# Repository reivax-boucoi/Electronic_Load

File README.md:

# Electronic Load

This repository hosts my work in developping a custom electronic load from scratch. 
For more information on what an electronic load does and what it can be used for, see [this](https://www.mouser.com/pdfdocs/DC_Electronic_Load_Application_Note.pdf). 

Specifically, this load targets DC-DC converters testing, as it includes input and output power monitoring.

I you have any question on this repository, feel free to contact the owner at (reivax[dot]boucoi[at]laposte[dot]net).

Featured on [Hackaday](https://hackaday.com/2020/06/06/a-diy-electronic-load-with-a-twist/) and [Electronics-Lab](https://www.electronics-lab.com/diy-electronic-load-dc-dc-converter-characterization/)!

---
---

### Features

* Constant Current, Power and Resistance modes
* Battery capacity logging with adjustable cutoff voltage
* Input and output power logging : instant efficiency reading for DC-DC converters
* Rotary encoder driven interface
* Dedicated Load ON/OFF button
* Intuitive LCD menu system with editable values
* 12bit current, voltage and power measurements 
* 30W continuous sinking capability, 250W peak
* Temperature controlled fan with auto shutdown.
* Adjustable acquistion rate
* 115200 bauds serial communication through USB with a PC (non-isolated !)

### Specifications
> Enough talk, give us the specs, son !

Altough the device has not been fully qualified through systematic testing, here are the basic specs you can expect. 
* Input voltage range : 0 - 100V DC maximum, 2-80V DC regulating
* Supply voltage range : 0 - 16V maximum, 12V nominal 
* Device current consumption : 50mA nominal (0.6W)
* Load current range : 5mA - 5.25A, in 8mA steps
* Current regulation : 5% +/- 8mA typical @ 8kHz bandwidth
* Transient response : rise time < 20µs/A, overshoot < 2%
* Constant Power/Resistance regulation bandwidth : 10Hz

---
---

## Schematic and Layout
The heart of the system is an Atmel ATmega328P AVR microcontroller with 32kB of Flash and 2k of RAM running at a whopping 16MHz. It interfaces an I2C 12bit DAC (the MCP47FEB21A1) and the LTC2992 dual power monitor chip.

The USB serial interface uses the MCP2221A bridge. The display is a classic 16x2 LCD.

On the analog part, 10mΩ  and 0.2Ω shunt resistors are used, coupled with two W9NK90Z N-ch power MOSFETS. The heatsink was salvaged from an old graphics card. Attached are a 10k NTC and a generic fan (12v @ 200mA, 80mm). Current regulation is achieved through the help of a MCP6H02 opamp, and a carefully designed feedback network which guarantees the specified rise time with little to no overshoot.

The layout was done using the Eagle software (v9.5.2). Gerbers, Eagle project files, top and bottom views are available on the `pcb` folder. PCBs were printed using JLCPCB service.
The schematic is available in a pdf and Eagle `.sch` format as well. A Bill of Materials (BOM) is also available, in plain text and html format, on the `pcb` folder.

Several user-definable bi-color status LEDs are included, such as Load ON/OFF, TX & RX, acquisition blink, as well as a power LED.

An expansion/debug port is provided, with +5V, ground, I2C and UART available.

There are several issues regarding the layout of the PCB, as it is a first version. Improper Kelvin connections to the current sense resistors, or wrong hole size for the power input connector by example. The heatsink originally used is salvaged from old equipement and the footprint may not be relevant to anyone else. Space for rubber feet placement should be included. Also, the LCD is too close to the heatsink, which is impractical during assembly (especially accessing the fan and temp sensor connector).

---
---

## Firmware
The firmware for this device is currently in revision 1.3. It is written for a barebone ATmega328p Atmel microcontroller.

```18604 bytes (60%) of program storage space. Maximum is 30720 bytes.```

```1635 bytes (79%) of dynamic memory, 413 bytes left. Maximum is 2048 bytes.```

As you can see it's not the lightest firmware, mostly due to the use of the `Wire` and `LCD` librairies from Arduino, which are bulky. However, there is still enough room for future improvements. Just keep in mind if you want to improve the project to leave space for local variables allocation.

---

### Programming
An ISP port is provided on the board, making reflashing easy. All you need is an AVR-compatible programmer with the standard 10 pins ICSP header. I used the very good (and very cheap!) [Usbasp](https://www.fischl.de/usbasp/) during developpement. Avrdude can be used to download the pre-compiled binary `main.hex`, or you can compile the project yourself first.
`Avr Fuses settings :(E:FD, H:DE, L:FF)`

To program the chip, execute : `avrdude -p m328p -c usbasp -P usb -U flash:w:firmware/main.hex`

---

### Software structure

* Display related stuff : `Screen.cpp`, `Menu.cpp`
* LTC2992 power monitoring stuff : `PM.cpp`
* DC Load stuff : `Load.cpp`
* Generic io interfacing : `Utils.cpp`, `SimpleRotary.cpp`, `Wire.cpp`, `LCD.cpp`
* Control loop and display update : `main.cpp`

---

### Usage
First apply power to the device through USB (for limited load capacity) or, better, 12V DC on the input power jack (beware of polarity).

The welcome screen pops up with the following menus : 

* Load allows you to set the load parameters and mode (CC/CP/CR)
* Battery enters the battery capacity mode
* Meter measures input power
* Settings is self explanatory

Turn the rotary encoder to cycle through the menus and screens, and push to enter. At any time use the back button (to the right of the encoder) to get back to the previous menu or exit editing mode. 

Editing a value starts by selecting the value to edit. Press enter on a screen, you should get a flashing square in front of a value. Turn the knob until the desired value is selected. Press enter to edit. The leftmost digit is selected. To change the edited digit, press enter once again. Press back to validate. 

**You will have to restart the load in order for the changes to take effect.** This is done to prevent happy little accidents. To start and stop the load, press the rightmost button. The blue LED should light up. Is the LED turns red, a fault occured. Faults can happen if :
* The heatsink temperature exceeds the hard temperature stop defined in `Load.h`
* The load fails to regulate. This will mostly be caused by the DUT hiccuping (or sharp V/I curve), or insufficent power to the Electronic Load.

The load menu has 4 screens : 

The last screen shows the power lost in the DUT (Pr), the efficency, the input and output voltages of the converter.

The load mode (CC/CP/CR) is determined by the screen displayed when the load is started. If the screen is not one of the CC/CP/CR screens, is starts in the previously used mode.

Here is what the Battery screen looks like :

Set the discharge current I and the cutoff voltage Vc before starting the load with the rightmost button. Accumulated capacity in Wh and Ah are displayed. The load will automatically shut off when the input voltage is below the cutoff voltage. The total capacity will remain displayed until the load is restarted in this mode.

The meter screen shows the input measurements :

The settings screen alows to modify various parameters : 

It monitors the supply voltage and you can change the threshold temperature for the fan, as well as the refresh rate of the screen. Note that the load has a hard temperature stop defined in `Load.h`, and a maximum refresh rate of approx 10Hz.

---
---

## Improvements

- [x] Design a mechanical mount for the fan / stabilize the board
- [x] Re-think the menu system to be more modular / lower size
- WIP Add logging capability with serial interface
- WIP Add current sweep programming for DC-DC converters automatic characterization (with di/dv auto resolution)
* Fix the minimum current issue (currently min is 5mA)
* Fix the 4 terminal Kelvin connection on the 10mΩ current sense resistors in the PCB layout
* Design a usb isolator companion board or add SD card logging addon on i2c bus.
* Design 4.5V->12V boost addon to allow full operation from usb power
* Better code commenting
* Save last used confguration on EEPROM for next power-up.
* ...

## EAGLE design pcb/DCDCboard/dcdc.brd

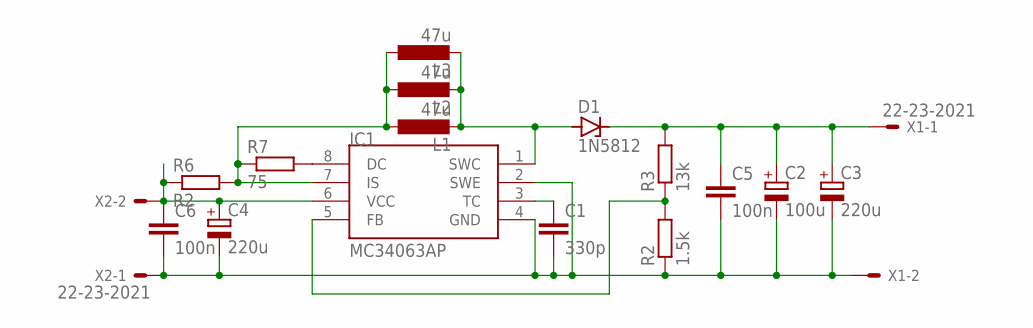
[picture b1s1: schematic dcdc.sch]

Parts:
C1: 330p; C0805
C2: 100u; E5-8,5
C3, C4: 220u; E5-8,5
C5, C6: 100n; C0805
D1: 1N5812; C1702-15
IC1: MC34063AP; DIL08
L1: 47u; TJ3-U2
L2: 47u; TJ4-U2
L3: 47u; 6000-XXXX-RC
R2: 1.5k; R0805
R3: 13k; 0204/7
R6: R2; R0805
R7: 75; R0805
X1, X2: 22-23-2021

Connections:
FB: IC1.5 (FB), R2.2, R3.1
GND: C1.2, C2.-, C3.-, C4.-, C5.2, C6.2, IC1.2 (SWE), IC1.4 (GND), R2.1, X1.2, X2.1
unnamed: IC1.8 (DC), R7.2
unnamed: IC1.7 (IS), L1.1, L2.1, L3.1, R6.2, R7.1
unnamed: C1.1, IC1.3 (TC)
SW: D1.A, IC1.1 (SWC), L1.2, L2.2, L3.2
VIN: C4.+, C6.1, IC1.6 (VCC), R6.1, X2.2
VOUT: C2.+, C3.+, C5.1, D1.C, R3.2, X1.1

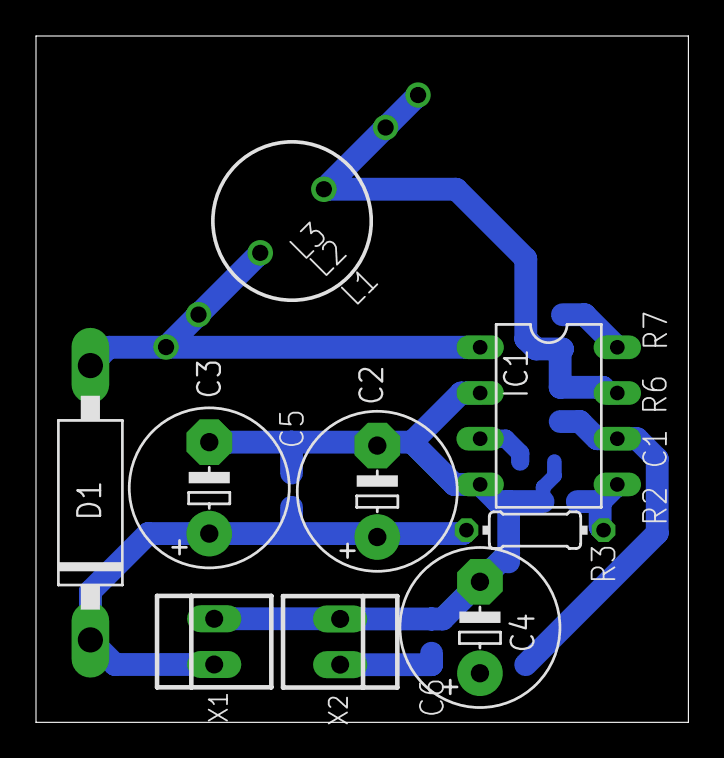
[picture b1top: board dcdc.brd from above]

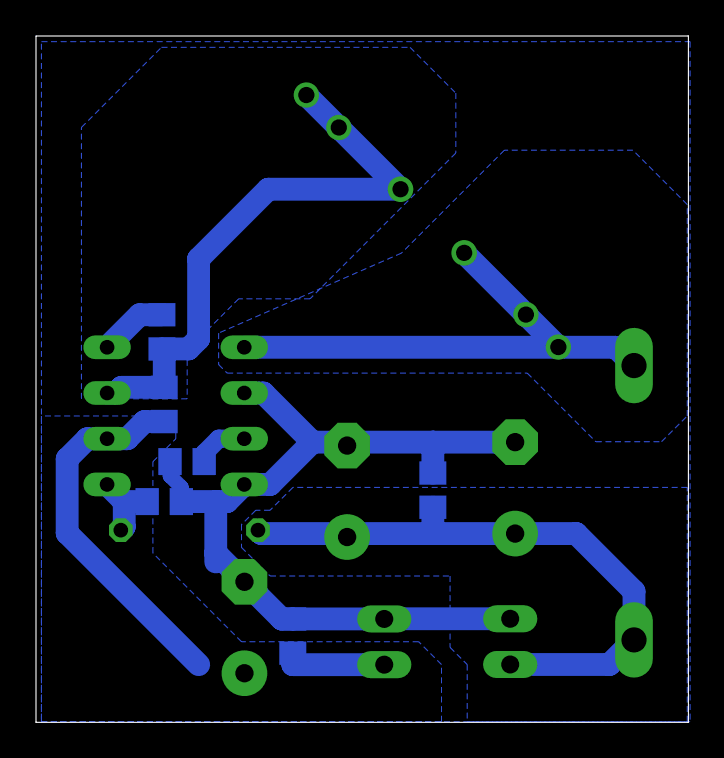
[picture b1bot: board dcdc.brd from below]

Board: 2 copper layers, 36.2 x 38.1 mm, 17 parts (6 on the bottom side), 8 nets.

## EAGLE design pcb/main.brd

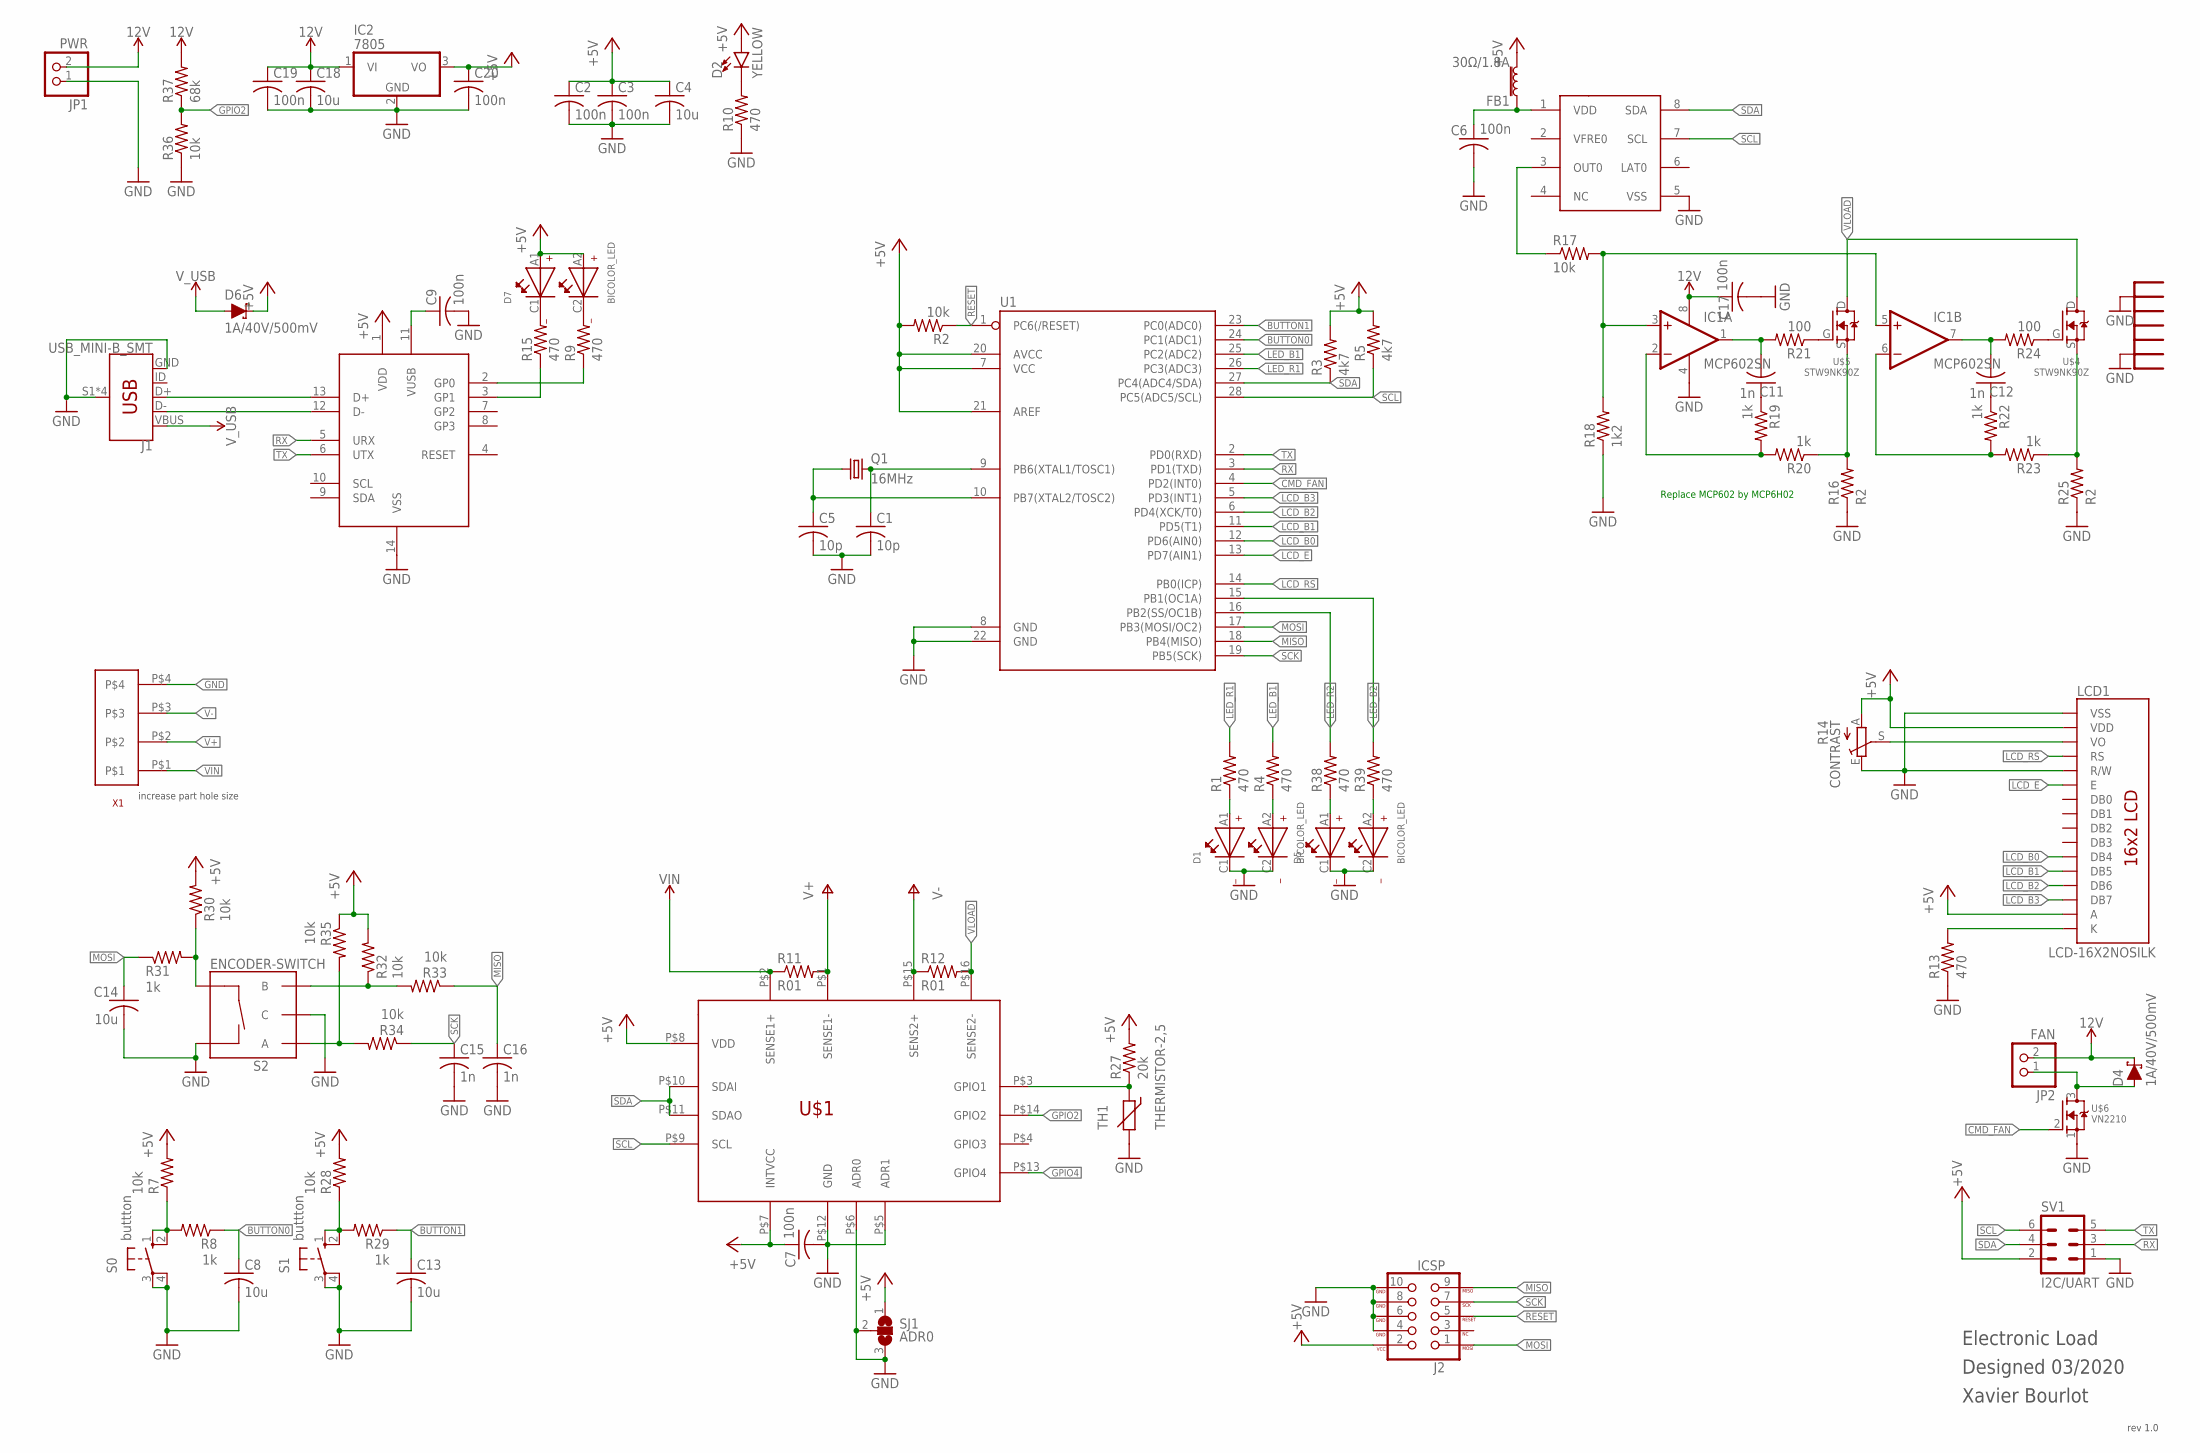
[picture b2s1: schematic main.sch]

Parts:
BR1: MCP2221A; DIP14
C1, C5: 10p; C0603
C2, C3, C6, C7, C9, C17, C19, C20: 100n; C0603
C4, C18: 10u; C1206
C8, C13, C14: 10u; C0603
C11, C12: 1n; C0805
C15, C16: 1n; C0603
D1, D5, D7: BICOLOR_LED
D2: YELLOW; LED_3MM
D4, D6: 1A/40V/500mV; SMA-DIODE
FB1: 30Ω/1.8A; 0603
IC1: MCP602SN; SO08
IC2: 7805; TO220V
J1: USB_MINI-B_SMT; USB-MINIB
J2: ICSP; 2X5-SHROUDED
JP1: PWR; 1X02
JP2: FAN; 1X02
LCD1: LCD-16X2NOSILK; LCD-16X2_NOSILK
Q1: 16MHz; HC49U70
R1, R4, R9, R10, R13, R15, R38, R39: 470; R0805
R2, R7, R17, R28, R30, R32, R33, R34, R35, R36: 10k; R0805
R3, R5: 4k7; R0805
R8, R19, R20, R22, R23, R29, R31: 1k; R0805
R11, R12: R01; R2512
R14: CONTRAST; RJ9W
R16, R25: R2; R2512
R18: 1k2; R0805
R21, R24: 100; R0805
R27: 20k; R0805
R37: 68k; R0805
S0, S1: buttton; B3F-10XX
S2: ENCODER-SWITCH; ROTARY_ENC_PLAIN
SJ1: ADR0; SJ_2
SV1: I2C/UART; MA03-2
TH1: THERMISTOR-2,5; RS-2,5
U1: 328P; DIP28
U$1: LTC2992; MSOP16
U$2: HEATSINK_0NOSILK; HEATSINK_01
U$3: MCP47FEB21; TSSOP8
U$4, U$5: STW9NK90Z; TO247BV
U$6: VN2210; TO92
X1: SCREWTERM_5MM_4WAY

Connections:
12V: C17.1, C18.1, C19.1, D4.C, IC1.8 (V+), IC2.1 (VI), JP1.2, JP2.2, R37.2
+5V: BR1.1 (VDD), C2.1, C3.1, C4.1, C7.1, C20.1, D2.A, D6.C, D7.A1, D7.A2, FB1.2, IC2.3 (VO), J2.2 (VCC), LCD1.2 (VDD), LCD1.15 (A), R2.2, R3.2, R5.2, R7.2, R14.A, R27.2, R28.2, R30.2, R32.2, R35.1, SJ1.1, SV1.2, U1.7 (VCC), U1.20 (AVCC), U1.21 (AREF), U$1.P$7 (INTVCC), U$1.P$8 (VDD)
B0: R7.1, R8.2, S0.1 (S), S0.2 (S1)
B1: R28.1, R29.2, S1.1 (S), S1.2 (S1)
BUTTON0: C8.1, R8.1, U1.24 (PC1(ADC1))
BUTTON1: C13.1, R29.1, U1.23 (PC0(ADC0))
CMD_FAN: U1.4 (PD2(INT0)), U$6.2 (G)
D+: BR1.13 (D+), J1.D+
D-: BR1.12 (D-), J1.D-
DAC_OUT: R17.1, U$3.3 (OUT0)
FANNEG: D4.A, JP2.1, U$6.3 (D)
GND: BR1.14 (VSS), C1.2, C2.2, C3.2, C4.2, C5.2, C6.2, C7.2, C8.2, C9.2, C13.2, C14.2, C15.2, C16.2, C17.2, C18.2, C19.2, C20.2, D1.C1, D1.C2, D5.C1, D5.C2, IC1.4 (V-), IC2.2 (GND), J1.GND, J1.S1 (SHIELD), J1.S2 (SHIELD), J1.S3 (SHIELD), J1.S4 (SHIELD), J2.4 (GND), J2.6 (GND), J2.8 (GND), J2.10 (GND), JP1.1, LCD1.1 (VSS), LCD1.5 (R/W), R10.1, R13.1, R14.E, R16.1, R18.1, R25.1, R36.1, S0.3, S0.4 (P1), S1.3, S1.4 (P1), S2.C, S2.SW-, SJ1.2, SJ1.3, SV1.1, TH1.2, U1.8 (GND), U1.22 (GND), U$1.P$5 (ADR1), U$1.P$6 (ADR0), U$1.P$12 (GND), U$2.P$1, U$2.P$2, U$3.5 (VSS), U$6.1 (S), X1.P$4
GPIO2: R36.2, R37.1, U$1.P$14 (GPIO2)
GPIO4: U$1.P$13 (GPIO4)
LCD1_CONTRAST: LCD1.3 (VO), R14.S
LCD1_K: LCD1.16 (K), R13.2
LCD_B0: LCD1.11 (DB4), U1.12 (PD6(AIN0))
LCD_B1: LCD1.12 (DB5), U1.11 (PD5(T1))
LCD_B2: LCD1.13 (DB6), U1.6 (PD4(XCK/T0))
LCD_B3: LCD1.14 (DB7), U1.5 (PD3(INT1))
LCD_E: LCD1.6 (E), U1.13 (PD7(AIN1))
LCD_RS: LCD1.4 (RS), U1.14 (PB0(ICP))
LED_B1: R4.2, U1.25 (PC2(ADC2))
LED_B2: R39.2, U1.15 (PB1(OC1A))
LED_R1: R1.2, U1.26 (PC3(ADC3))
LED_R2: R38.2, U1.16 (PB2(SS/OC1B))
MISO: C16.1, J2.9 (MISO), R33.1, U1.18 (PB4(MISO))
MOSI: C14.1, J2.1 (MOSI), R31.1, U1.17 (PB3(MOSI/OC2))
unnamed: C1.1, Q1.2, U1.9 (PB6(XTAL1/TOSC1))
unnamed: C5.1, Q1.1, U1.10 (PB7(XTAL2/TOSC2))
unnamed: C6.1, FB1.1, U$3.1 (VDD)
unnamed: D5.A1, R38.1
unnamed: D5.A2, R39.1
unnamed: D1.A1, R1.1
unnamed: R21.1, U$5.G
unnamed: D1.A2, R4.1
unnamed: BR1.2 (GP0), R9.1
unnamed: BR1.11 (VUSB), C9.1
unnamed: BR1.3 (GP1), R15.1
unnamed: D7.C1, R15.2
unnamed: D7.C2, R9.2
unnamed: D2.K (C), R10.2
unnamed: C11.1, R19.1
unnamed: C12.1, R22.1
RESET: J2.5 (RESET), R2.1, U1.1 (PC6(/RESET))
RX: BR1.5 (URX), SV1.3, U1.3 (PD1(TXD))
SCK: C15.1, J2.7 (SCK), R34.1, U1.19 (PB5(SCK))
SCL: R5.1, SV1.6, U1.28 (PC5(ADC5/SCL)), U$1.P$9 (SCL), U$3.7 (SCL)
SDA: R3.1, SV1.4, U1.27 (PC4(ADC4/SDA)), U$1.P$10 (SDAI), U$1.P$11 (SDAO), U$3.8 (SDA)
TX: BR1.6 (UTX), SV1.5, U1.2 (PD0(RXD))
V+: R11.2, U$1.P$1 (SENSE1-), X1.P$2
V-: R12.1, U$1.P$15 (SENS2+), X1.P$3
VCTRL: IC1.3 (+IN), IC1.5 (+IN), R17.2, R18.2
VENC: R30.1, R31.2, S2.SW+
VENCA: R34.2, R35.2, S2.A
VENCB: R32.1, R33.2, S2.B
VFB1: IC1.2 (-IN), R19.2, R20.2
VFB2: IC1.6 (-IN), R22.2, R23.2
VG2: R24.1, U$4.G
VIN: R11.1, U$1.P$2 (SENSE1+), X1.P$1
VLOAD: R12.2, U$1.P$16 (SENSE2-), U$4.D, U$5.D
VO1: C11.2, IC1.1 (OUT), R21.2
VO2: C12.2, IC1.7 (OUT), R24.2
VS1: R16.2, R20.1, U$5.S
VS2: R23.1, R25.2, U$4.S
VT: R27.1, TH1.1, U$1.P$3 (GPIO1)
V_USB: D6.A, J1.VBUS

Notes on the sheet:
Replace MCP602 by MCP6H02
Electronic Load
Designed 03/2020
Xavier Bourlot
rev 1.0
increase part hole size

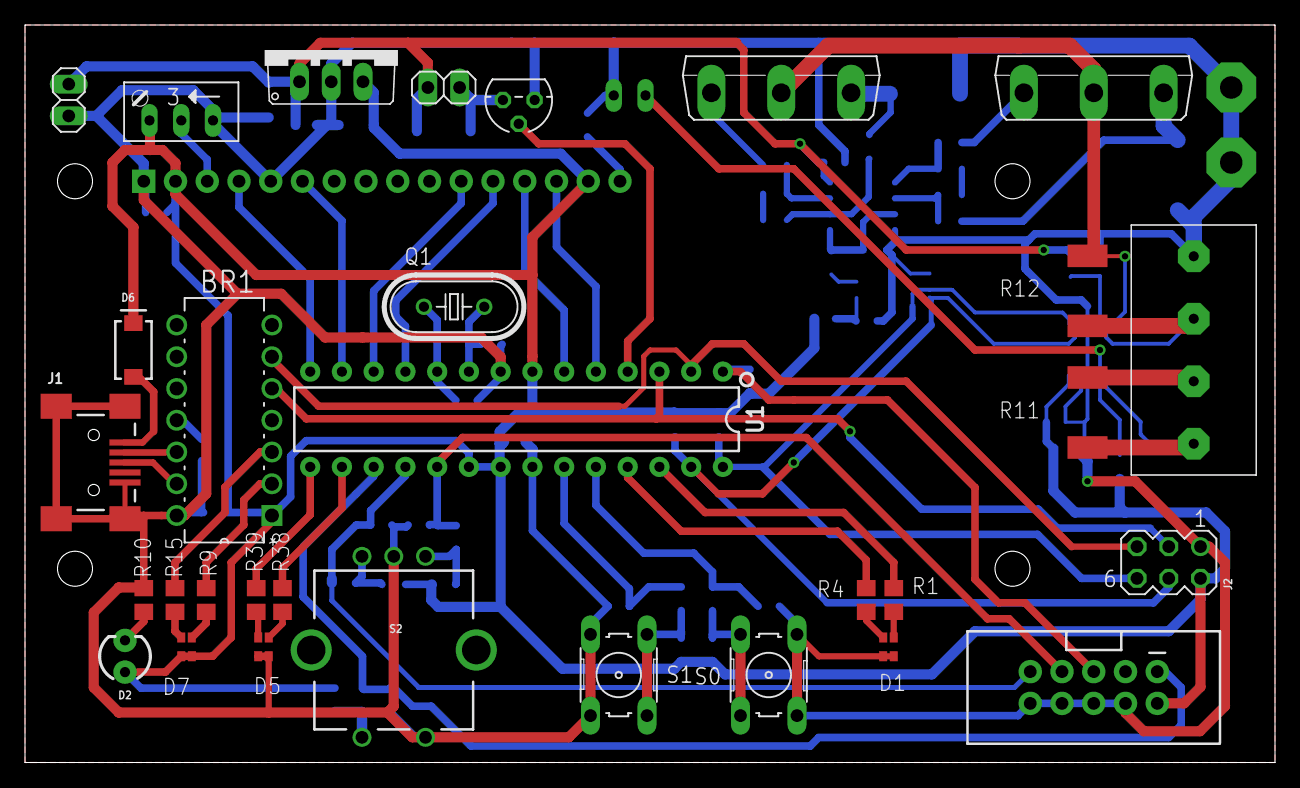
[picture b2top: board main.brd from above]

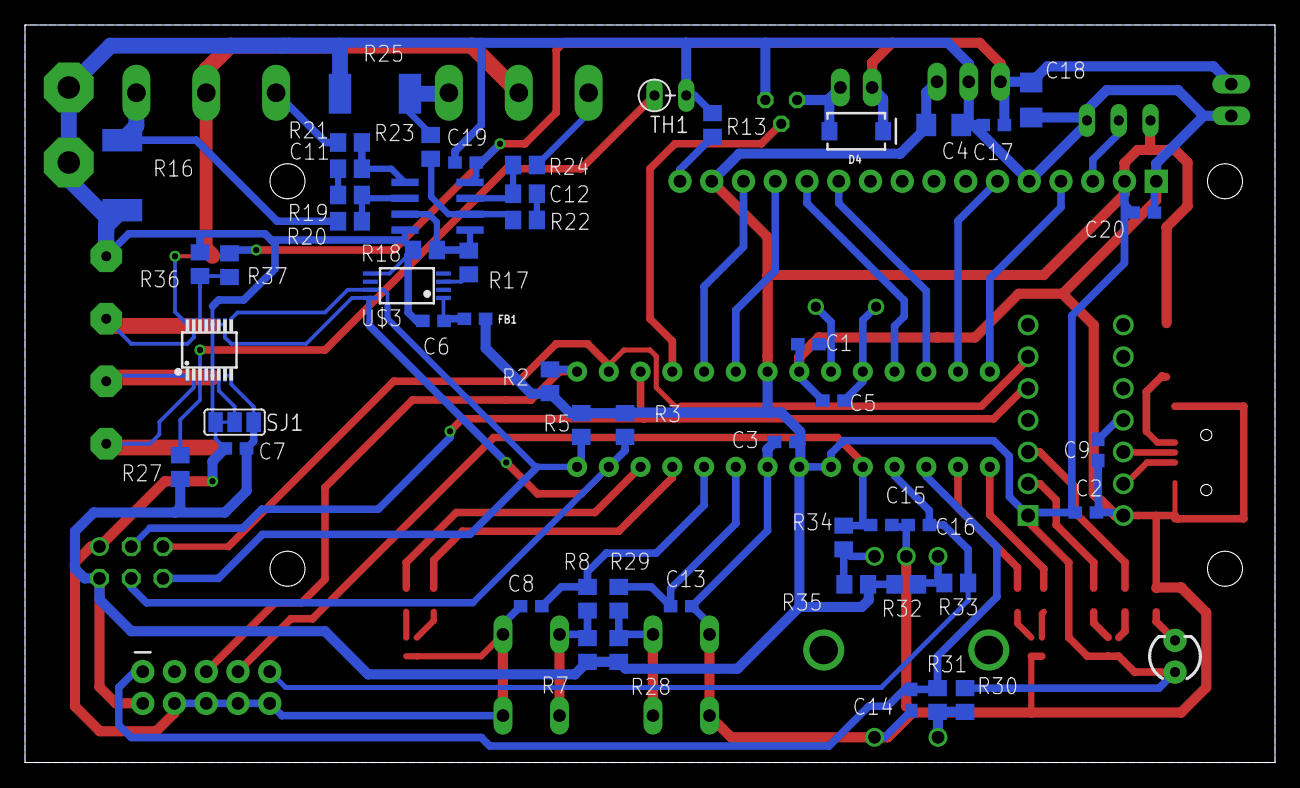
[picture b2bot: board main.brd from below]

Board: 2 copper layers, 100.0 x 59.0 mm, 86 parts (53 on the bottom side), 66 nets.

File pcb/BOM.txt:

Qty	Value	Device	Package	Parts	Description	MPN	REF
2	100	R-US_R0805	R0805	"R21, R24"	RESISTOR		
8	100n	C-USC0603	C0603	"C2, C3, C6, C7, C9, C17, C19, C20"	CAPACITOR		
10	10k	R-US_R0805	R0805	"R2, R7, R17, R28, R30, R32, R33, R34, R35, R36"	RESISTOR		
2	10p	C-USC0603	C0603	"C1, C5"	CAPACITOR		
3	10u	C-USC0603	C0603	"C8, C13, C14"	CAPACITOR		
2	10u	C-USC1206	C1206	"C4, C18"	CAPACITOR		
1	16MHz	CRYSTALHC49U70	HC49U70	Q1	CRYSTAL		
2	1A/40V/500mV	DIODE-SCHOTTKY-SS14	SMA-DIODE	"D4, D6"	Schottky diode	DIO-08053	
7	1k	R-US_R0805	R0805	"R8, R19, R20, R22, R23, R29, R31"	RESISTOR		
1	1k2	R-US_R0805	R0805	R18	RESISTOR		
2	1n	C-USC0603	C0603	"C15, C16"	CAPACITOR		
2	1n	C-USC0805	C0805	"C11, C12"	CAPACITOR		
1	20k	R-US_R0805	R0805	R27	RESISTOR		
1	30?/1.8A	FERRITE_BEAD-0603	603	FB1	"Ferrite Bead (blocks, cores, rings, chokes, etc.)"	NDUC-07859	
1	328P	ATMEGA328P_PDIP	DIP28	U1	Atmel 328P	IC-09136	
8	470	R-US_R0805	R0805	"R1, R4, R9, R10, R13, R15, R38, R39"	RESISTOR		
2	4k7	R-US_R0805	R0805	"R3, R5"	RESISTOR		
1	68k	R-US_R0805	R0805	R37	RESISTOR		
1	7805	786TV	TO220V	IC2	Positive VOLTAGE REGULATOR		
1	ADR0	SJ2W	SJ_2	SJ1	SMD solder JUMPER		
3	BICOLOR_LED	BICOLOR_LED	BICOLOR_LED	"D1, D5, D7"	dual 0603 generic		
1	CONTRAST	TRIM_EU-RJ9W	RJ9W	R14	POTENTIOMETER		
1	ENCODER-SWITCH	ENCODER-SWITCH	ROTARY_ENC_PLAIN	S2	Rotary Encoder w/ Select Switch	COM-09117	
1	FAN	PINHD-1X2	1X02	JP2	PIN HEADER		
1	HEATSINK_0NOSILK	HEATSINK_0NOSILK	HEATSINK_01	U$2	Custom heatsink		
1	I2C/UART	MA03-2	MA03-2	SV1	PIN HEADER		
1	ICSP	AVR_SPI_PROG_5X2PTH2	2X5-SHROUDED	J2	AVR 10-pin ICSP Header	CONN-08671	PRT-08506
1	LCD-16X2NOSILK	LCD-16X2NOSILK	LCD-16X2_NOSILK	LCD1	Standard text-only 16x2 parallel input LCD		LCD-00255
1	LTC2992	LTC2992	MSOP16	U$1	Dual supply monitor		
1	MCP2221A	MCP2221A	DIP14	BR1	Usb to uart bridge		
1	MCP47FEB21	MCP47FEB21	TSSOP8	U$3	Dac		
1	MCP602SN	MCP602SN	SO08	IC1	Single Op Amp 2.7V to 6.0V Single Supply CMOS		
1	PWR	PINHD-1X2	1X02	JP1	PIN HEADER		
2	R01	R-US_R2512	R2512	"R11, R12"	RES 0.01 OHM 1% 1W 2512	TL3AR01F	
2	R2	R-US_R2512	R2512	"R16, R25"	RES 0.2 OHM 1% 2W 2512	RLP73K3AR20FTDF	
1		SCREWTERM_5MM_4WAY		X1			
2	STW9NK90Z	STW9NK90Z	TO247BV	"U$4, U$5"			
1	"THERMISTOR-2,5"	"THERMISTOR-2,5"	"RS-2,5"	TH1	THERMISTOR		
1	USB_MINI-B_SMT	USB_MINI-B_SMT	USB-MINIB	J1	USB type Mini-B Connector	CONN-08193	PRT-00587
1	VN2210	VN2210	TO92	U$6			
1	YELLOW	LED3MM	LED_3MM	D2	LED (Generic)	DIO-08794	
2	buttton	10-XX	B3F-10XX	"S0, S1"	OMRON SWITCH	B3F-1000	176432

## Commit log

2020-05-06 added screenshots
2020-05-25 added datasheets
2020-05-29 added project files
2020-06-01 added programming instructions
2020-06-01 added image test
2020-06-01 updated asembled picture
2020-10-19 Removed interface
2020-10-20 updated load toboard selection
2020-10-21 updated PM to selection of boards
2020-10-22 added board define
2020-10-23 removed debug prints
2020-10-24 moved
2020-10-25 -madded raw soft
2020-10-26 moved files around

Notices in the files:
parts and their libraries:
SparkFun-LED: Licensing: Creative Commons ShareAlike 4.0 International - https://creativecommons.org/licenses/by-sa/4.0
